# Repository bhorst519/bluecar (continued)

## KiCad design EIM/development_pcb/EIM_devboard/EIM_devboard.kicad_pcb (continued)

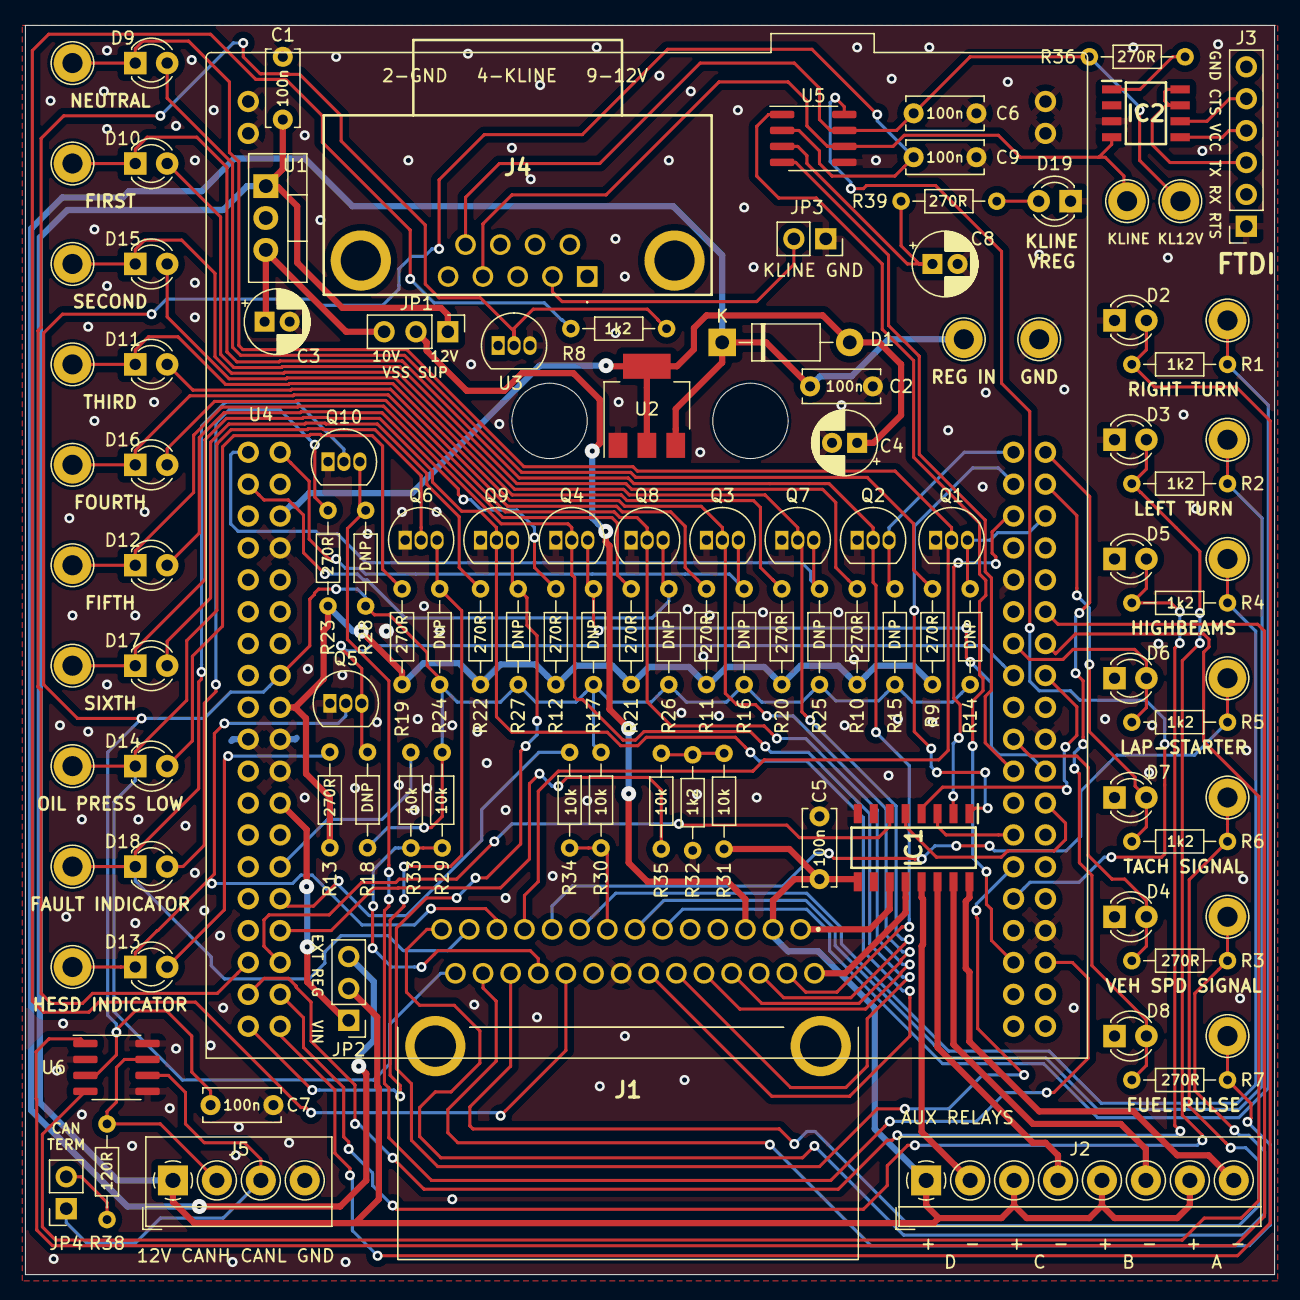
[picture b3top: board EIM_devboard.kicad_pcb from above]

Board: 2 copper layers, 99.5 x 99.5 mm, 114 parts (0 on the bottom side), 90 nets.

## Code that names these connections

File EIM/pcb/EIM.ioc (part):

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Mcu.Name=STM32F429ZITx
Mcu.Package=LQFP144
Mcu.UserName=STM32F429ZITx
PA0/WKUP.Signal=ADCx_IN0
PA1.Signal=ADCx_IN1
PA10.Mode=Asynchronous
PA10.Signal=USART1_RX
PA11.Mode=CAN_Activate
PA11.Signal=CAN1_RX
PA12.Mode=CAN_Activate
PA12.Signal=CAN1_TX
PA13.Mode=JTAG_5_pins
PA13.Signal=SYS_JTMS-SWDIO
PA14.Mode=JTAG_5_pins
PA14.Signal=SYS_JTCK-SWCLK
PA15.Mode=JTAG_5_pins
PA15.Signal=SYS_JTDI
PA2.Signal=ADCx_IN2
PA3.Signal=ADCx_IN3
PA4.Signal=ADCx_IN4
PA5.Signal=ADCx_IN5
PA6.Signal=ADCx_IN6
PA7.Signal=ADCx_IN7
PA9.Mode=Asynchronous
PA9.Signal=USART1_TX
PB0.Signal=ADCx_IN8
PB1.Signal=ADCx_IN9
PB10.Mode=Asynchronous
PB10.Signal=USART3_TX
PB11.Mode=Asynchronous
PB11.Signal=USART3_RX
PB12.Mode=CAN_Activate
PB12.Signal=CAN2_RX
PB13.Mode=CAN_Activate
PB13.Signal=CAN2_TX
PB14.Mode=Full_Duplex_Master
PB14.Signal=SPI2_MISO
PB15.Mode=Full_Duplex_Master
PB15.Signal=SPI2_MOSI
PB2/BOOT1.GPIOParameters=GPIO_Label
PB2/BOOT1.GPIO_Label=PB2
PB2/BOOT1.Signal=GPIO_Input
PB3.Mode=JTAG_5_pins
PB3.Signal=SYS_JTDO-SWO
PB4.Mode=JTAG_5_pins
PB4.Signal=SYS_JTRST
PB5.GPIOParameters=GPIO_Label
PB5.GPIO_Label=VSS
PB5.Signal=GPXTI5
PB6.Mode=I2C
PB6.Signal=I2C1_SCL
PB7.Mode=I2C
PB7.Signal=I2C1_SDA
PB8.GPIOParameters=GPIO_Label
PB8.GPIO_Label=LED1
PB8.Signal=S_TIM4_CH3
PB9.GPIOParameters=GPIO_Label
PB9.GPIO_Label=LED2_B
PB9.Signal=S_TIM4_CH4
PC0.Signal=ADCx_IN10
PC1.Signal=ADCx_IN11
PC10.Mode=Asynchronous
PC10.Signal=UART4_TX
PC11.Mode=Asynchronous
PC11.Signal=UART4_RX
PC14/OSC32_IN.Mode=LSE-External-Clock-Source
PC14/OSC32_IN.Signal=RCC_OSC32_IN
PC15/OSC32_OUT.Mode=LSE-External-Clock-Source
PC15/OSC32_OUT.Signal=RCC_OSC32_OUT
PC2.Signal=ADCx_IN12
PC3.Signal=ADCx_IN13
PC4.GPIOParameters=GPIO_Label
PC4.GPIO_Label=VSS
PC4.Signal=GPXTI4
PC5.GPIOParameters=GPIO_Label
PC5.GPIO_Label=FAULT_IND
PC5.Signal=GPIO_Input
PD12.GPIOParameters=GPIO_Label
PD12.GPIO_Label=LED2_R
PD12.Signal=S_TIM4_CH1
PD13.GPIOParameters=GPIO_Label
PD13.GPIO_Label=LED2_G
PD13.Signal=S_TIM4_CH2
PD3.Mode=Full_Duplex_Master
PD3.Signal=SPI2_SCK
PD4.GPIOParameters=GPIO_Label
PD4.GPIO_Label=RS485_DIR
PD4.Signal=GPIO_Output
PD5.Mode=Asynchronous
PD5.Signal=USART2_TX
PD6.Mode=Asynchronous
PD6.Signal=USART2_RX
PE10.GPIOParameters=GPIO_Label
PE10.GPIO_Label=THIRD
PE10.Signal=GPXTI10
PE11.GPIOParameters=GPIO_Label
PE11.GPIO_Label=SECOND
PE11.Signal=GPIO_Input
PE12.GPIOParameters=GPIO_Label
PE12.GPIO_Label=FIRST
PE12.Signal=GPIO_Input
PE13.GPIOParameters=GPIO_Label
PE13.GPIO_Label=HL_RLY_EN
PE13.Signal=GPIO_Output
PE14.GPIOParameters=GPIO_Label
PE14.GPIO_Label=LAP_RLY_EN
PE14.Signal=GPIO_Output
PE7.GPIOParameters=GPIO_Label
PE7.GPIO_Label=SIXTH
PE7.Signal=GPIO_Input
PE8.GPIOParameters=GPIO_Label
PE8.GPIO_Label=FIFTH
PE8.Signal=GPIO_Input
PE9.GPIOParameters=GPIO_Label
PE9.GPIO_Label=FOURTH
PE9.Signal=GPIO_Input
PF10.GPIOParameters=GPIO_Label
PF10.GPIO_Label=HORN_EN
PF10.Signal=GPIO_Output
PF11.GPIOParameters=GPIO_Label
PF11.GPIO_Label=OIL_P_LOW
PF11.Signal=GPIO_Input
PF12.GPIOParameters=GPIO_Label
PF12.GPIO_Label=TACH
PF12.Signal=GPXTI12
PF13.GPIOParameters=GPIO_Label
PF13.GPIO_Label=NEUTRAL
PF13.Signal=GPIO_Input
PF14.GPIOParameters=GPIO_Label
PF14.GPIO_Label=LOWBEAM
PF14.Signal=GPIO_Input
PF15.GPIOParameters=GPIO_Label
PF15.GPIO_Label=HIGHBEAM
PF15.Signal=GPIO_Input
PF2.GPIOParameters=GPIO_Label
PF2.GPIO_Label=KLINE_EN
PF2.Signal=GPIO_Output
PF3.GPIOParameters=GPIO_Label
PF3.GPIO_Label=MAIN_RLY_EN
PF3.Signal=GPIO_Output
PF4.GPIOParameters=GPIO_Label
PF4.GPIO_Label=ENG_ON_EN
PF4.Signal=GPIO_Output
PF5.GPIOParameters=GPIO_Label
PF5.GPIO_Label=ENG_START_EN
PF5.Signal=GPIO_Output
PF6.GPIOParameters=GPIO_Label
PF6.GPIO_Label=BRAKE_LIGHT_EN
PF6.Signal=GPXTI6
PF7.GPIOParameters=GPIO_Label
PF7.GPIO_Label=HIGHBEAM_EN
PF7.Signal=GPIO_Output
PF8.GPIOParameters=GPIO_Label
PF8.GPIO_Label=L_TURN_SIG_EN
PF8.Signal=GPIO_Output
PF9.GPIOParameters=GPIO_Label
PF9.GPIO_Label=R_TURN_SIG_EN
PF9.Signal=GPIO_Output
PG0.GPIOParameters=GPIO_Label
PG0.GPIO_Label=TURN_L
PG0.Signal=GPIO_Input
PG1.GPIOParameters=GPIO_Label
PG1.GPIO_Label=TURN_R
PG1.Signal=GPIO_Input
PH0/OSC_IN.Mode=HSE-External-Clock-Source
PH0/OSC_IN.Signal=RCC_OSC_IN
PH1/OSC_OUT.Mode=HSE-External-Clock-Source
PH1/OSC_OUT.Signal=RCC_OSC_OUT
RCC.HSE_VALUE=25000000
RCC.SYSCLKFreq_VALUE=16000000
board=custom

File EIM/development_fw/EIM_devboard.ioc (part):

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Mcu.Name=STM32F103R(8-B)Tx
Mcu.Package=LQFP64
Mcu.UserName=STM32F103RBTx
PA0-WKUP.GPIOParameters=GPIO_Label
PA0-WKUP.GPIO_Label=TEMP
PA0-WKUP.Signal=ADCx_IN0
PA1.GPIOParameters=GPIO_Label
PA1.GPIO_Label=FUEL
PA1.Signal=ADCx_IN1
PA10.GPIOParameters=GPIO_PuPd
PA10.GPIO_PuPd=GPIO_PULLUP
PA10.Mode=Asynchronous
PA10.Signal=USART1_RX
PA11.Mode=CAN_Activate
PA11.Signal=CAN_RX
PA12.Mode=CAN_Activate
PA12.Signal=CAN_TX
PA13.GPIOParameters=GPIO_Label
PA13.GPIO_Label=TMS
PA13.Mode=Serial_Wire
PA13.Signal=SYS_JTMS-SWDIO
PA14.GPIOParameters=GPIO_Label
PA14.GPIO_Label=TCK
PA14.Mode=Serial_Wire
PA14.Signal=SYS_JTCK-SWCLK
PA2.GPIOParameters=GPIO_Speed,GPIO_PuPd,GPIO_Label,GPIO_Mode
PA2.GPIO_Label=USART_TX
PA2.GPIO_Mode=GPIO_MODE_AF_PP
PA2.GPIO_PuPd=GPIO_NOPULL
PA2.GPIO_Speed=GPIO_SPEED_FREQ_LOW
PA2.Mode=Asynchronous
PA2.Signal=USART2_TX
PA3.GPIOParameters=GPIO_Speed,GPIO_PuPd,GPIO_Label,GPIO_Mode
PA3.GPIO_Label=USART_RX
PA3.GPIO_Mode=GPIO_MODE_AF_PP
PA3.GPIO_PuPd=GPIO_NOPULL
PA3.GPIO_Speed=GPIO_SPEED_FREQ_LOW
PA3.Mode=Asynchronous
PA3.Signal=USART2_RX
PA4.GPIOParameters=GPIO_Label
PA4.GPIO_Label=BATT_12V_ADC
PA4.Signal=ADCx_IN4
PA5.GPIOParameters=GPIO_Speed,GPIO_PuPd,GPIO_Label,GPIO_ModeDefaultOutputPP
PA5.GPIO_Label=LD2 [Green Led]
PA5.GPIO_ModeDefaultOutputPP=GPIO_MODE_OUTPUT_PP
PA5.GPIO_PuPd=GPIO_NOPULL
PA5.GPIO_Speed=GPIO_SPEED_FREQ_LOW
PA5.Signal=GPIO_Output
PA6.GPIOParameters=GPIO_PuPd,GPIO_Label
PA6.GPIO_Label=LAP-STARTER
PA6.GPIO_PuPd=GPIO_PULLDOWN
PA6.Signal=GPIO_Input
PA7.GPIOParameters=GPIO_PuPd,GPIO_Label
PA7.GPIO_Label=HESD
PA7.GPIO_PuPd=GPIO_PULLDOWN
PA7.Signal=GPIO_Input
PA9.Mode=Asynchronous
PA9.Signal=USART1_TX
PB0.GPIOParameters=GPIO_Label
PB0.GPIO_Label=HEADLIGHT_RELAY
PB0.Signal=GPIO_Output
PB1.GPIOParameters=GPIO_Label
PB1.GPIO_Label=LAP_RELAY
PB1.Signal=GPIO_Output
PB10.GPIOParameters=GPIO_Label
PB10.GPIO_Label=RELAY_C
PB10.Signal=GPIO_Output
PB12.GPIOParameters=GPIO_Label
PB12.GPIO_Label=RELAY_D
PB12.Signal=GPIO_Output
PB13.Mode=Full_Duplex_Master
PB13.Signal=SPI2_SCK
PB14.Mode=Full_Duplex_Master
PB14.Signal=SPI2_MISO
PB15.Mode=Full_Duplex_Master
PB15.Signal=SPI2_MOSI
PB2.GPIOParameters=GPIO_PuPd,GPIO_Label
PB2.GPIO_Label=FIFTH
PB2.GPIO_PuPd=GPIO_PULLUP
PB2.Signal=GPIO_Input
PB3.GPIOParameters=GPIO_Label
PB3.GPIO_Label=SWO
PB3.Signal=SYS_JTDO-TRACESWO
PB4.GPIOParameters=GPIO_PuPd,GPIO_Label
PB4.GPIO_Label=SIXTH
PB4.GPIO_PuPd=GPIO_PULLUP
PB4.Signal=GPIO_Input
PB5.GPIOParameters=GPIO_PuPd,GPIO_Label
PB5.GPIO_Label=MCP2021_FLT
PB5.GPIO_PuPd=GPIO_PULLUP
PB5.Signal=GPIO_Input
PB6.Mode=I2C
PB6.Signal=I2C1_SCL
PB7.Mode=I2C
PB7.Signal=I2C1_SDA
PB8.GPIOParameters=GPIO_Label
PB8.GPIO_Label=RELAY_A
PB8.Signal=GPIO_Output
PB9.GPIOParameters=GPIO_Label
PB9.GPIO_Label=RELAY_B
PB9.Signal=GPIO_Output
PC0.GPIOParameters=GPIO_PuPd,GPIO_Label
PC0.GPIO_Label=TURN_R
PC0.GPIO_PuPd=GPIO_PULLDOWN
PC0.Signal=GPIO_Input
PC1.GPIOParameters=GPIO_PuPd,GPIO_Label
PC1.GPIO_Label=TURN_L
PC1.GPIO_PuPd=GPIO_PULLDOWN
PC1.Signal=GPIO_Input
PC10.GPIOParameters=GPIO_PuPd,GPIO_Label
PC10.GPIO_Label=SECOND
PC10.GPIO_PuPd=GPIO_PULLUP
PC10.Signal=GPIO_Input
PC11.GPIOParameters=GPIO_PuPd,GPIO_Label
PC11.GPIO_Label=THIRD
PC11.GPIO_PuPd=GPIO_PULLUP
PC11.Signal=GPIO_Input
PC12.GPIOParameters=GPIO_PuPd,GPIO_Label
PC12.GPIO_Label=FOURTH
PC12.GPIO_PuPd=GPIO_PULLUP
PC12.Signal=GPIO_Input
PC13-TAMPER-RTC.GPIOParameters=GPIO_PuPd,GPIO_Label
PC13-TAMPER-RTC.GPIO_Label=B1 [Blue PushButton]
PC13-TAMPER-RTC.GPIO_PuPd=GPIO_NOPULL
PC13-TAMPER-RTC.Signal=GPXTI13
PC14-OSC32_IN.Mode=LSE-External-Oscillator
PC14-OSC32_IN.Signal=RCC_OSC32_IN
PC15-OSC32_OUT.Mode=LSE-External-Oscillator
PC15-OSC32_OUT.Signal=RCC_OSC32_OUT
PC2.GPIOParameters=GPIO_PuPd,GPIO_Label
PC2.GPIO_Label=HIGHBEAM
PC2.GPIO_PuPd=GPIO_PULLDOWN
PC2.Signal=GPIO_Input
PC3.GPIOParameters=GPIO_PuPd,GPIO_Label
PC3.GPIO_Label=OIL
PC3.GPIO_PuPd=GPIO_PULLDOWN
PC3.Signal=GPIO_Input
PC4.GPIOParameters=GPIO_PuPd,GPIO_Label
PC4.GPIO_Label=FAULT_INDICATOR
PC4.GPIO_PuPd=GPIO_PULLDOWN
PC4.Signal=GPIO_Input
PC5.GPIOParameters=GPIO_PuPd,GPIO_Label
PC5.GPIO_Label=NEUTRAL
PC5.GPIO_PuPd=GPIO_PULLUP
PC5.Signal=GPIO_Input
PC6.GPIOParameters=GPIO_PuPd,GPIO_Label,GPIO_ModeDefaultEXTI
PC6.GPIO_Label=TA_SIG
PC6.GPIO_ModeDefaultEXTI=GPIO_MODE_IT_RISING
PC6.GPIO_PuPd=GPIO_PULLDOWN
PC6.Signal=GPXTI6
PC7.GPIOParameters=GPIO_PuPd,GPIO_Label,GPIO_ModeDefaultEXTI
PC7.GPIO_Label=SP_SIG
PC7.GPIO_ModeDefaultEXTI=GPIO_MODE_IT_RISING
PC7.GPIO_PuPd=GPIO_PULLDOWN
PC7.Signal=GPXTI7
PC8.GPIOParameters=GPIO_Label
PC8.GPIO_Label=FUEL_PULSE
PC8.Signal=GPXTI8
PC9.GPIOParameters=GPIO_PuPd,GPIO_Label
PC9.GPIO_Label=FIRST
PC9.GPIO_PuPd=GPIO_PULLUP
PC9.Signal=GPIO_Input
PD0-OSC_IN.Mode=HSE-External-Clock-Source
PD0-OSC_IN.Signal=RCC_OSC_IN
PD1-OSC_OUT.Mode=HSE-External-Clock-Source
PD1-OSC_OUT.Signal=RCC_OSC_OUT
RCC.SYSCLKFreq_VALUE=64000000
RCC.SYSCLKSource=RCC_SYSCLKSOURCE_PLLCLK
board=NUCLEO-F103RB
boardIOC=true

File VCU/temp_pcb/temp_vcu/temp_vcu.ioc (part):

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Mcu.Name=STM32F439Z(G-I)Tx
Mcu.Package=LQFP144
Mcu.UserName=STM32F439ZITx
PA1.GPIOParameters=GPIO_Label
PA1.GPIO_Label=RMII_REF_CLK [LAN8742A-CZ-TR_REFCLK0]
PA1.Mode=RMII
PA1.Signal=ETH_REF_CLK
PA10.GPIOParameters=GPIO_Label
PA10.GPIO_Label=USB_ID
PA10.Signal=USB_OTG_FS_ID
PA11.GPIOParameters=GPIO_Label
PA11.GPIO_Label=USB_DM
PA11.Mode=Device_Only
PA11.Signal=USB_OTG_FS_DM
PA12.GPIOParameters=GPIO_Label
PA12.GPIO_Label=USB_DP
PA12.Mode=Device_Only
PA12.Signal=USB_OTG_FS_DP
PA13.GPIOParameters=GPIO_Label
PA13.GPIO_Label=TMS
PA13.Mode=Serial_Wire
PA13.Signal=SYS_JTMS-SWDIO
PA14.GPIOParameters=GPIO_Label
PA14.GPIO_Label=TCK
PA14.Mode=Serial_Wire
PA14.Signal=SYS_JTCK-SWCLK
PA2.GPIOParameters=GPIO_Label
PA2.GPIO_Label=RMII_MDIO [LAN8742A-CZ-TR_MDIO]
PA2.Mode=RMII
PA2.Signal=ETH_MDIO
PA3.GPIOParameters=GPIO_Label
PA3.GPIO_Label=APS1
PA3.Signal=ADCx_IN3
PA7.GPIOParameters=GPIO_Label
PA7.GPIO_Label=RMII_CRS_DV [LAN8742A-CZ-TR_CRS_DV]
PA7.Mode=RMII
PA7.Signal=ETH_CRS_DV
PA8.GPIOParameters=GPIO_Label
PA8.GPIO_Label=USB_SOF [TP1]
PA8.Mode=Activate_SOF_FS
PA8.Signal=USB_OTG_FS_SOF
PA9.GPIOParameters=GPIO_Label
PA9.GPIO_Label=USB_VBUS
PA9.Mode=Activate_VBUS
PA9.Signal=USB_OTG_FS_VBUS
PB0.GPIOParameters=GPIO_Label
PB0.GPIO_Label=LD1 [Green]
PB0.Signal=GPIO_Output
PB13.GPIOParameters=GPIO_Label
PB13.GPIO_Label=RMII_TXD1 [LAN8742A-CZ-TR_TXD1]
PB13.Mode=RMII
PB13.Signal=ETH_TXD1
PB14.GPIOParameters=GPIO_Label
PB14.GPIO_Label=LD3 [Red]
PB14.Signal=GPIO_Output
PB7.GPIOParameters=GPIO_Label
PB7.GPIO_Label=LD2 [Blue]
PB7.Signal=GPIO_Output
PC0.GPIOParameters=GPIO_Label
PC0.GPIO_Label=APS2
PC0.Signal=ADCx_IN10
PC1.GPIOParameters=GPIO_Label
PC1.GPIO_Label=RMII_MDC [LAN8742A-CZ-TR_MDC]
PC1.Mode=RMII
PC1.Signal=ETH_MDC
PC13.GPIOParameters=GPIO_Label
PC13.GPIO_Label=USER_Btn [B1]
PC13.Signal=GPXTI13
PC14/OSC32_IN.Mode=LSE-External-Oscillator
PC14/OSC32_IN.Signal=RCC_OSC32_IN
PC15/OSC32_OUT.Mode=LSE-External-Oscillator
PC15/OSC32_OUT.Signal=RCC_OSC32_OUT
PC3.GPIOParameters=GPIO_Label
PC3.GPIO_Label=BRAKE_SWITCH
PC3.Signal=GPIO_Input
PC4.GPIOParameters=GPIO_Label
PC4.GPIO_Label=RMII_RXD0 [LAN8742A-CZ-TR_RXD0]
PC4.Mode=RMII
PC4.Signal=ETH_RXD0
PC5.GPIOParameters=GPIO_Label
PC5.GPIO_Label=RMII_RXD1 [LAN8742A-CZ-TR_RXD1]
PC5.Mode=RMII
PC5.Signal=ETH_RXD1
PD0.Mode=CAN_Activate
PD0.Signal=CAN1_RX
PD1.Mode=CAN_Activate
PD1.Signal=CAN1_TX
PD6.GPIOParameters=GPIO_Label
PD6.GPIO_Label=LED2
PD6.Signal=GPIO_Output
PD7.GPIOParameters=GPIO_Label
PD7.GPIO_Label=LED1
PD7.Signal=GPIO_Output
PD8.GPIOParameters=GPIO_Label
PD8.GPIO_Label=STLK_RX [STM32F103CBT6_PA3]
PD8.Mode=Asynchronous
PD8.Signal=USART3_TX
PD9.GPIOParameters=GPIO_Label
PD9.GPIO_Label=STLK_TX [STM32F103CBT6_PA2]
PD9.Mode=Asynchronous
PD9.Signal=USART3_RX
PF10.GPIOParameters=GPIO_Label
PF10.GPIO_Label=USER_SWITCH
PF10.Signal=GPIO_Input
PF3.GPIOParameters=GPIO_Label
PF3.GPIO_Label=ENG_ENABLE
PF3.Signal=GPIO_Input
PF5.GPIOParameters=GPIO_Label
PF5.GPIO_Label=ENG_START
PF5.Signal=GPIO_Input
PG11.GPIOParameters=GPIO_Label
PG11.GPIO_Label=RMII_TX_EN [LAN8742A-CZ-TR_TXEN]
PG11.Mode=RMII
PG11.Signal=ETH_TX_EN
PG13.GPIOParameters=GPIO_Label
PG13.GPIO_Label=RMII_TXD0 [LAN8742A-CZ-TR_TXD0]
PG13.Mode=RMII
PG13.Signal=ETH_TXD0
PG6.GPIOParameters=GPIO_Label
PG6.GPIO_Label=USB_PowerSwitchOn [STMPS2151STR_EN]
PG6.Signal=GPIO_Output
PG7.GPIOParameters=GPIO_Label
PG7.GPIO_Label=USB_OverCurrent [STMPS2151STR_FAULT]
PG7.Signal=GPIO_Input
PH0/OSC_IN.GPIOParameters=GPIO_Label
PH0/OSC_IN.GPIO_Label=MCO [STM32F103CBT6_PA8]
PH0/OSC_IN.Mode=HSE-External-Clock-Source
PH0/OSC_IN.Signal=RCC_OSC_IN
PH1/OSC_OUT.Mode=HSE-External-Clock-Source
PH1/OSC_OUT.Signal=RCC_OSC_OUT
RCC.HSE_VALUE=8000000
RCC.SYSCLKFreq_VALUE=168000000
RCC.SYSCLKSource=RCC_SYSCLKSOURCE_PLLCLK
RCC.SYSCLKSourceVirtual=RCC_SYSCLKSOURCE_PLLCLK
board=NUCLEO-F439ZI
boardIOC=true

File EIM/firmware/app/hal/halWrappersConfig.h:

#ifndef HAL_WRAPPERS_CONFIG_H
#define HAL_WRAPPERS_CONFIG_H

#ifdef __cplusplus
extern "C" {
#endif

/***************************************************************************************************
*                                         I N C L U D E S                                          *
***************************************************************************************************/
#include "stm32f4xx_hal.h"

/***************************************************************************************************
*                                         T Y P E D E F S                                          *
***************************************************************************************************/
typedef enum
{
    // Outputs
    GPIO_MAIN_RELAY_EN,         // To power engine controller
    GPIO_HEADLIGHT_RELAY_EN,
    GPIO_ENG_ON_EN,             // To enable engine run/crank
    GPIO_ENG_START_EN,          // To crank engine
    GPIO_BRAKE_LIGHT_EN,
    GPIO_TURN_R_EN,
    GPIO_TURN_L_EN,
    GPIO_HIGH_BEAM_EN,
    GPIO_HORN_EN,
    GPIO_KLINE_EN,
    GPIO_KLINE_TX,
    GPIO_KLINE_RX,
    GPIO_SERVO_COMM_DIR,
    GPIO_SERVO_TX,
    GPIO_SERVO_RX,
    // Inputs
    GPIO_TACH,                  // Needs PWM-in/timer to determine RPM
    GPIO_GEAR_N,
    GPIO_GEAR_1,
    GPIO_GEAR_2,
    GPIO_GEAR_3,
    GPIO_GEAR_4,
    GPIO_GEAR_5,
    GPIO_GEAR_6,
    GPIO_TURN_R,
    GPIO_TURN_L,
    GPIO_LOW_BEAM,
    GPIO_HIGH_BEAM,
    GPIO_FAULT_IND,
    GPIO_OIL_P_LOW,
    MAX_NUM_GPIO
} HalWrappers_Gpio_E;

typedef enum
{
    PWM_LED_1,
    PWM_LED_2R,
    PWM_LED_2G,
    PWM_LED_2B,
    MAX_NUM_PWM
} HalWrappers_Pwm_E;

typedef enum
{
    ANALOG_12V,
    ANALOG_SERVO_12V,
    ANALOG_ENG_12V,
    ANALOG_ENG_TEMP,
    ANALOG_FUEL_LEVEL,
    ANALOG_FUEL_LOW,
    ANALOG_EXTRA,
    ANALOG_DIE_TEMP,
    ANALOG_ENG_ON_ISENSE,
    ANALOG_ENG_START_ISENSE,
    ANALOG_BRAKE_LIGHT_ISENSE,
    ANALOG_TURN_R_ISENSE,
    ANALOG_TURN_L_ISENSE,
    ANALOG_HIGH_BEAM_ISENSE,
    ANALOG_HORN_ISENSE,
    MAX_NUM_ANALOG
} HalWrappers_Analog_E;

typedef enum
{
    CAN_1,
    CAN_2,
    MAX_NUM_CAN
} HalWrappers_Can_E;

typedef enum
{
    SERIAL_KLINE,
    SERIAL_SERVO,
    MAX_NUM_SERIAL
} HalWrappers_Serial_E;

typedef struct
{
    ADC_HandleTypeDef * pAdc;
    TIM_HandleTypeDef * pPwmTim;
    TIM_HandleTypeDef * pUsTim;
    CAN_HandleTypeDef * pCan[MAX_NUM_CAN];
    UART_HandleTypeDef * pSerial[MAX_NUM_SERIAL];
} HalWrappers_Config_S;

#ifdef __cplusplus
}
#endif

#endif // HAL_WRAPPERS_CONFIG_H

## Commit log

2024-06-09 Board ready to order
2024-06-11 Ordered version of EIM dev board
2024-07-14 Working CAN demo
2024-07-15 Working gear check and CAN message
2024-07-30 Working printf to terminal and interrupt test
2024-08-16 Working K-Line wakeup & state request
2024-09-22 Initial working comms test
2024-09-23 Sterling's project start
2024-09-25 added lots of kline captures from ECU tool
2024-09-30 DBC parser and code gen - WIP receiver
2024-10-20 DBC parser and code gen - WIP receiver
    Periodic CAN transmit demo
    CAN receive demo
2024-11-25 HAL wrapper cleanup
    Kline interface module
    UART support
2024-11-26 Kline data conversions
2024-11-30 CPP (and C) template
2024-12-09 EIM schematic nearly complete. Missing ADC inputs and MCU pin assignments.
2024-12-16 CPP (and C) template
    Move modules to CPP
2024-12-16 WIP throttle module
2024-12-20 added Arjun's comments, assigned some MCU pins
2025-01-06 Throttle servo module
2025-01-08 Layout 75% done, before 8V bus deletion
2025-01-09 servo cleanup
2025-01-09 message modules
2025-01-09 task object
2025-01-09 unified app object
2025-01-09 add DataChannel locks
2025-01-11 jinja code gen templates
2025-01-11 jinja cleanup
2025-01-11 DBC updates
2025-01-11 RX/TX module infra
2025-01-12 fixing mistakes I found
2025-01-12 All components placed and pins assigned.
2025-01-13 EIM board complete - awaiting DR
2025-01-13 SNA definitions for DBC
2025-01-13 qualifiedVal util
2025-01-14 make CAN codegen C++
    support accepting QualifiedVal arguments
2025-01-14 update status qualifiers for servo data
2025-01-14 update status qualifiers for kline data
2025-01-15 Updated small things to make DRC pass without errors or warnings
2025-01-15 Board data as ordered on 1-15-25
2025-01-18 qualifiedVal cleanup
2025-01-18 Configure microsecond counter
2025-01-19 CPU profiler for task time/period
    CPU profiler for load
2025-01-19 better template
2025-01-20 set servo position demo
2025-01-20 more selective compiler flags
2025-01-20 add CAN codegen into build system
2025-02-08 EIM/development_X delete
2025-02-08 move EIM stm project
2025-02-08 add FreeRTOS to EIM
2025-02-08 EIM initial code gen
2025-02-12 Added pdf of ordered version
2025-02-15 project dev
2025-03-04 Add all GPIO to HAL abstraction
2025-03-04 Core at 180MHz
2025-03-04 EIM app
2025-03-04 relay test
2025-03-16 ADC conversion bringup
2025-03-16 ADC profiler
    Transmit initial ADC info
2025-03-16 add 100Hz task and do ADC stuff there
2025-03-16 filter ADC values
2025-03-17 halWrappers refactor
2025-03-18 halWrappers updates for stersmithNucleoMvp
2025-03-18 agree on 'uart' over 'serial'
2025-03-22 minor docs update
2025-03-23 More ADC conversions
2025-03-23 fix brake en pin config
2025-03-23 fix third pin config
2025-03-24 CAN interfaces for GPOs
2025-03-24 add GPIs
2025-04-06 Attempt EIM servo comms
    Time-based interrupts, using microsecond timer
2025-04-06 Debug servo comms
2025-04-09 reorganize dbc
2025-04-09 more analog signals TX-ed
2025-04-09 more more analog signals TX-ed
2025-04-09 bonus digital signals also TX-ed
2025-04-13 configure tach interrupt
2025-04-14 tach module
    shift dbc min/max to account for SNAs
2025-04-20 K-Line comms
2025-04-21 Completed schematic - ready for layout
2025-04-21 Shared kline and servo modules
2025-04-22 Ordered version of board
2025-04-23 Added pdf
2025-04-26 initial bringup
2025-04-26 better filtering for CAN RX signals
2025-04-27 periodic code
2025-04-27 configure tim5 as uSec timer
2025-04-27 configure can1 for 500k with RX interrupts
2025-04-27 configure ADC interrupts
2025-04-27 configure tim5 interrupts
2025-04-27 halWrappers config
2025-04-27 sorted signals/messages for CAN code gen
2025-04-27 add VCU to dbc
    documentation for message ID format
2025-04-27 signs of life - blink
2025-04-27 hook in generated CAN code with CanModule and TxModule
2025-04-28 codegen cleanup
    set signals SNA on init
2025-04-28 more ADC
2025-04-29 AdcModule for VCU
2025-04-29 IoIntModule for VCU
2025-04-29 TX IO and ADC data
2025-04-29 prototype VCU <-> EIM comms
2025-04-30 VCU ApsModule for pedal position
2025-05-01 EIM ThrottleModule for servo position
2025-05-04 EIM to PT rename
2025-05-05 add message cycle times
2025-05-05 CANdb++ wants to align VAL_ order with signal definition order
2025-05-05 generate message cycle times
2025-05-05 generate message receive timeouts
2025-05-15 limit throttle
2025-05-15 build script tweaks
2025-05-15 test
2025-05-17 re-arrange
2025-05-17 more error checking
2025-05-17 support signal SNA default of None
2025-05-18 support .dbc.json
2025-05-18 fixes from drive testing
2025-05-18 update to build actions
2025-05-18 proper value table extraction from DBCs
2025-05-21 smol dbc codegen cleanup
2025-05-21 Taylor series for mapping pedal position
2025-11-09 updated params
